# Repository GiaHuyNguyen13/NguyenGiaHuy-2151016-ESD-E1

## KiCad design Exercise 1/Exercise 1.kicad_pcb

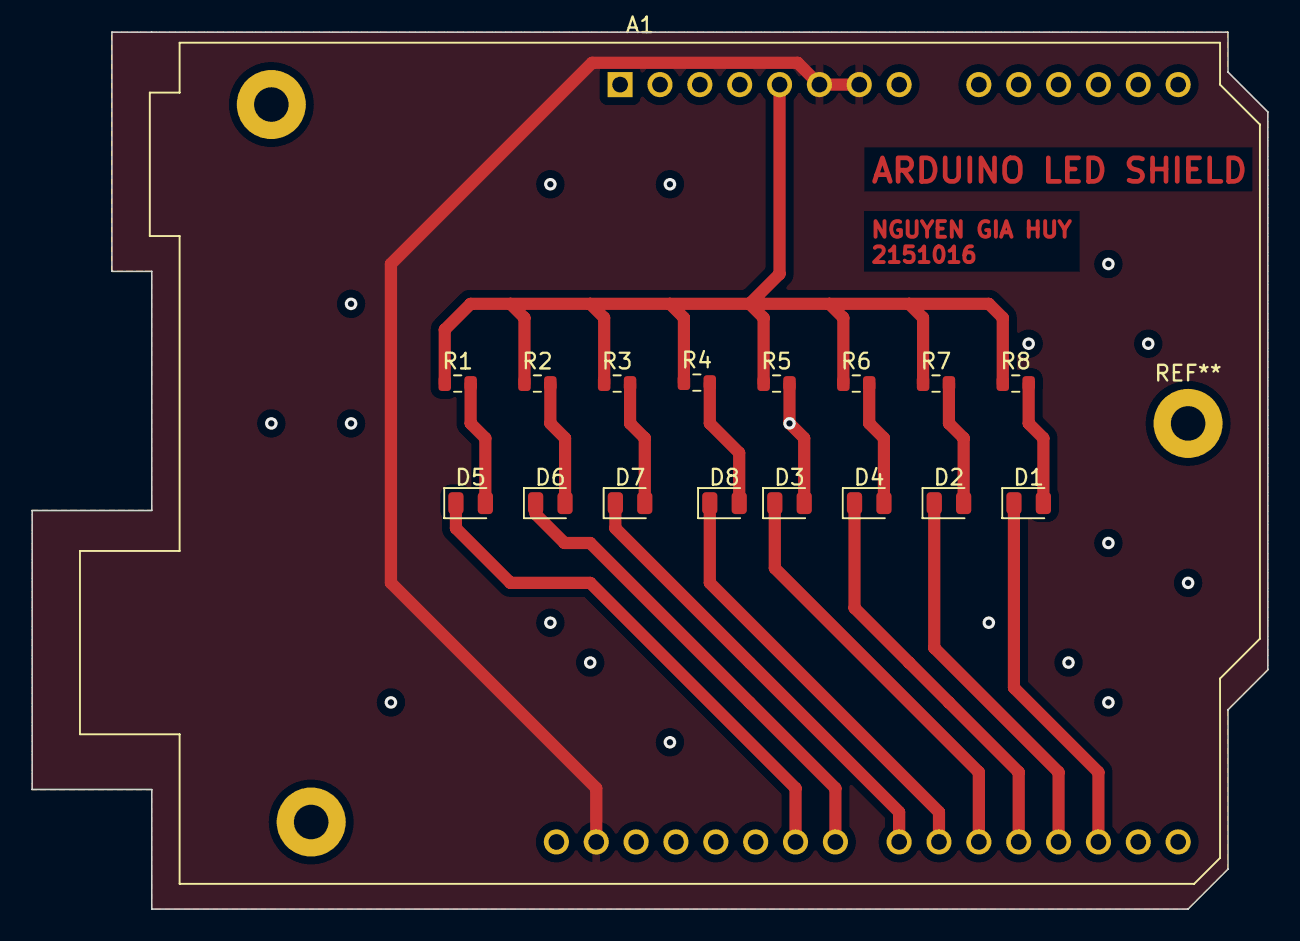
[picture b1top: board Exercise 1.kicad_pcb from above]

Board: 2 copper layers, 78.7 x 55.9 mm, 17 parts (0 on the bottom side), 18 nets.

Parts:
A1: Arduino_UNO_R2
D1, D2, D3, D4, D5, D6, D7, D8: LED; LED_0805_2012Metric
R1, R2, R3, R4, R5, R6, R7, R8: 247; R_0603_1608Metric

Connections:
GND: A1.6 (GND), A1.7 (GND), A1.29 (GND)
unnamed: A1.5 (+5V), R1.1, R2.1, R3.1, R4.1, R5.1, R6.1, R7.1, R8.1
unnamed: A1.17 (D2), D1.1 (K)
unnamed: A1.18 (D3), D2.1 (K)
unnamed: A1.19 (D4), D4.1 (K)
unnamed: A1.20 (D5), D3.1 (K)
unnamed: A1.21 (D6), D8.1 (K)
unnamed: A1.22 (D7), D7.1 (K)
unnamed: A1.23 (D8), D6.1 (K)
unnamed: A1.24 (D9), D5.1 (K)
unnamed: D1.2 (A), R8.2
unnamed: D2.2 (A), R7.2
unnamed: D3.2 (A), R5.2
unnamed: D4.2 (A), R6.2
unnamed: D5.2 (A), R1.2
unnamed: D6.2 (A), R2.2
unnamed: D7.2 (A), R3.2
unnamed: D8.2 (A), R4.2

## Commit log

2024-01-12 Rename Conner view.png to Corner view.png
